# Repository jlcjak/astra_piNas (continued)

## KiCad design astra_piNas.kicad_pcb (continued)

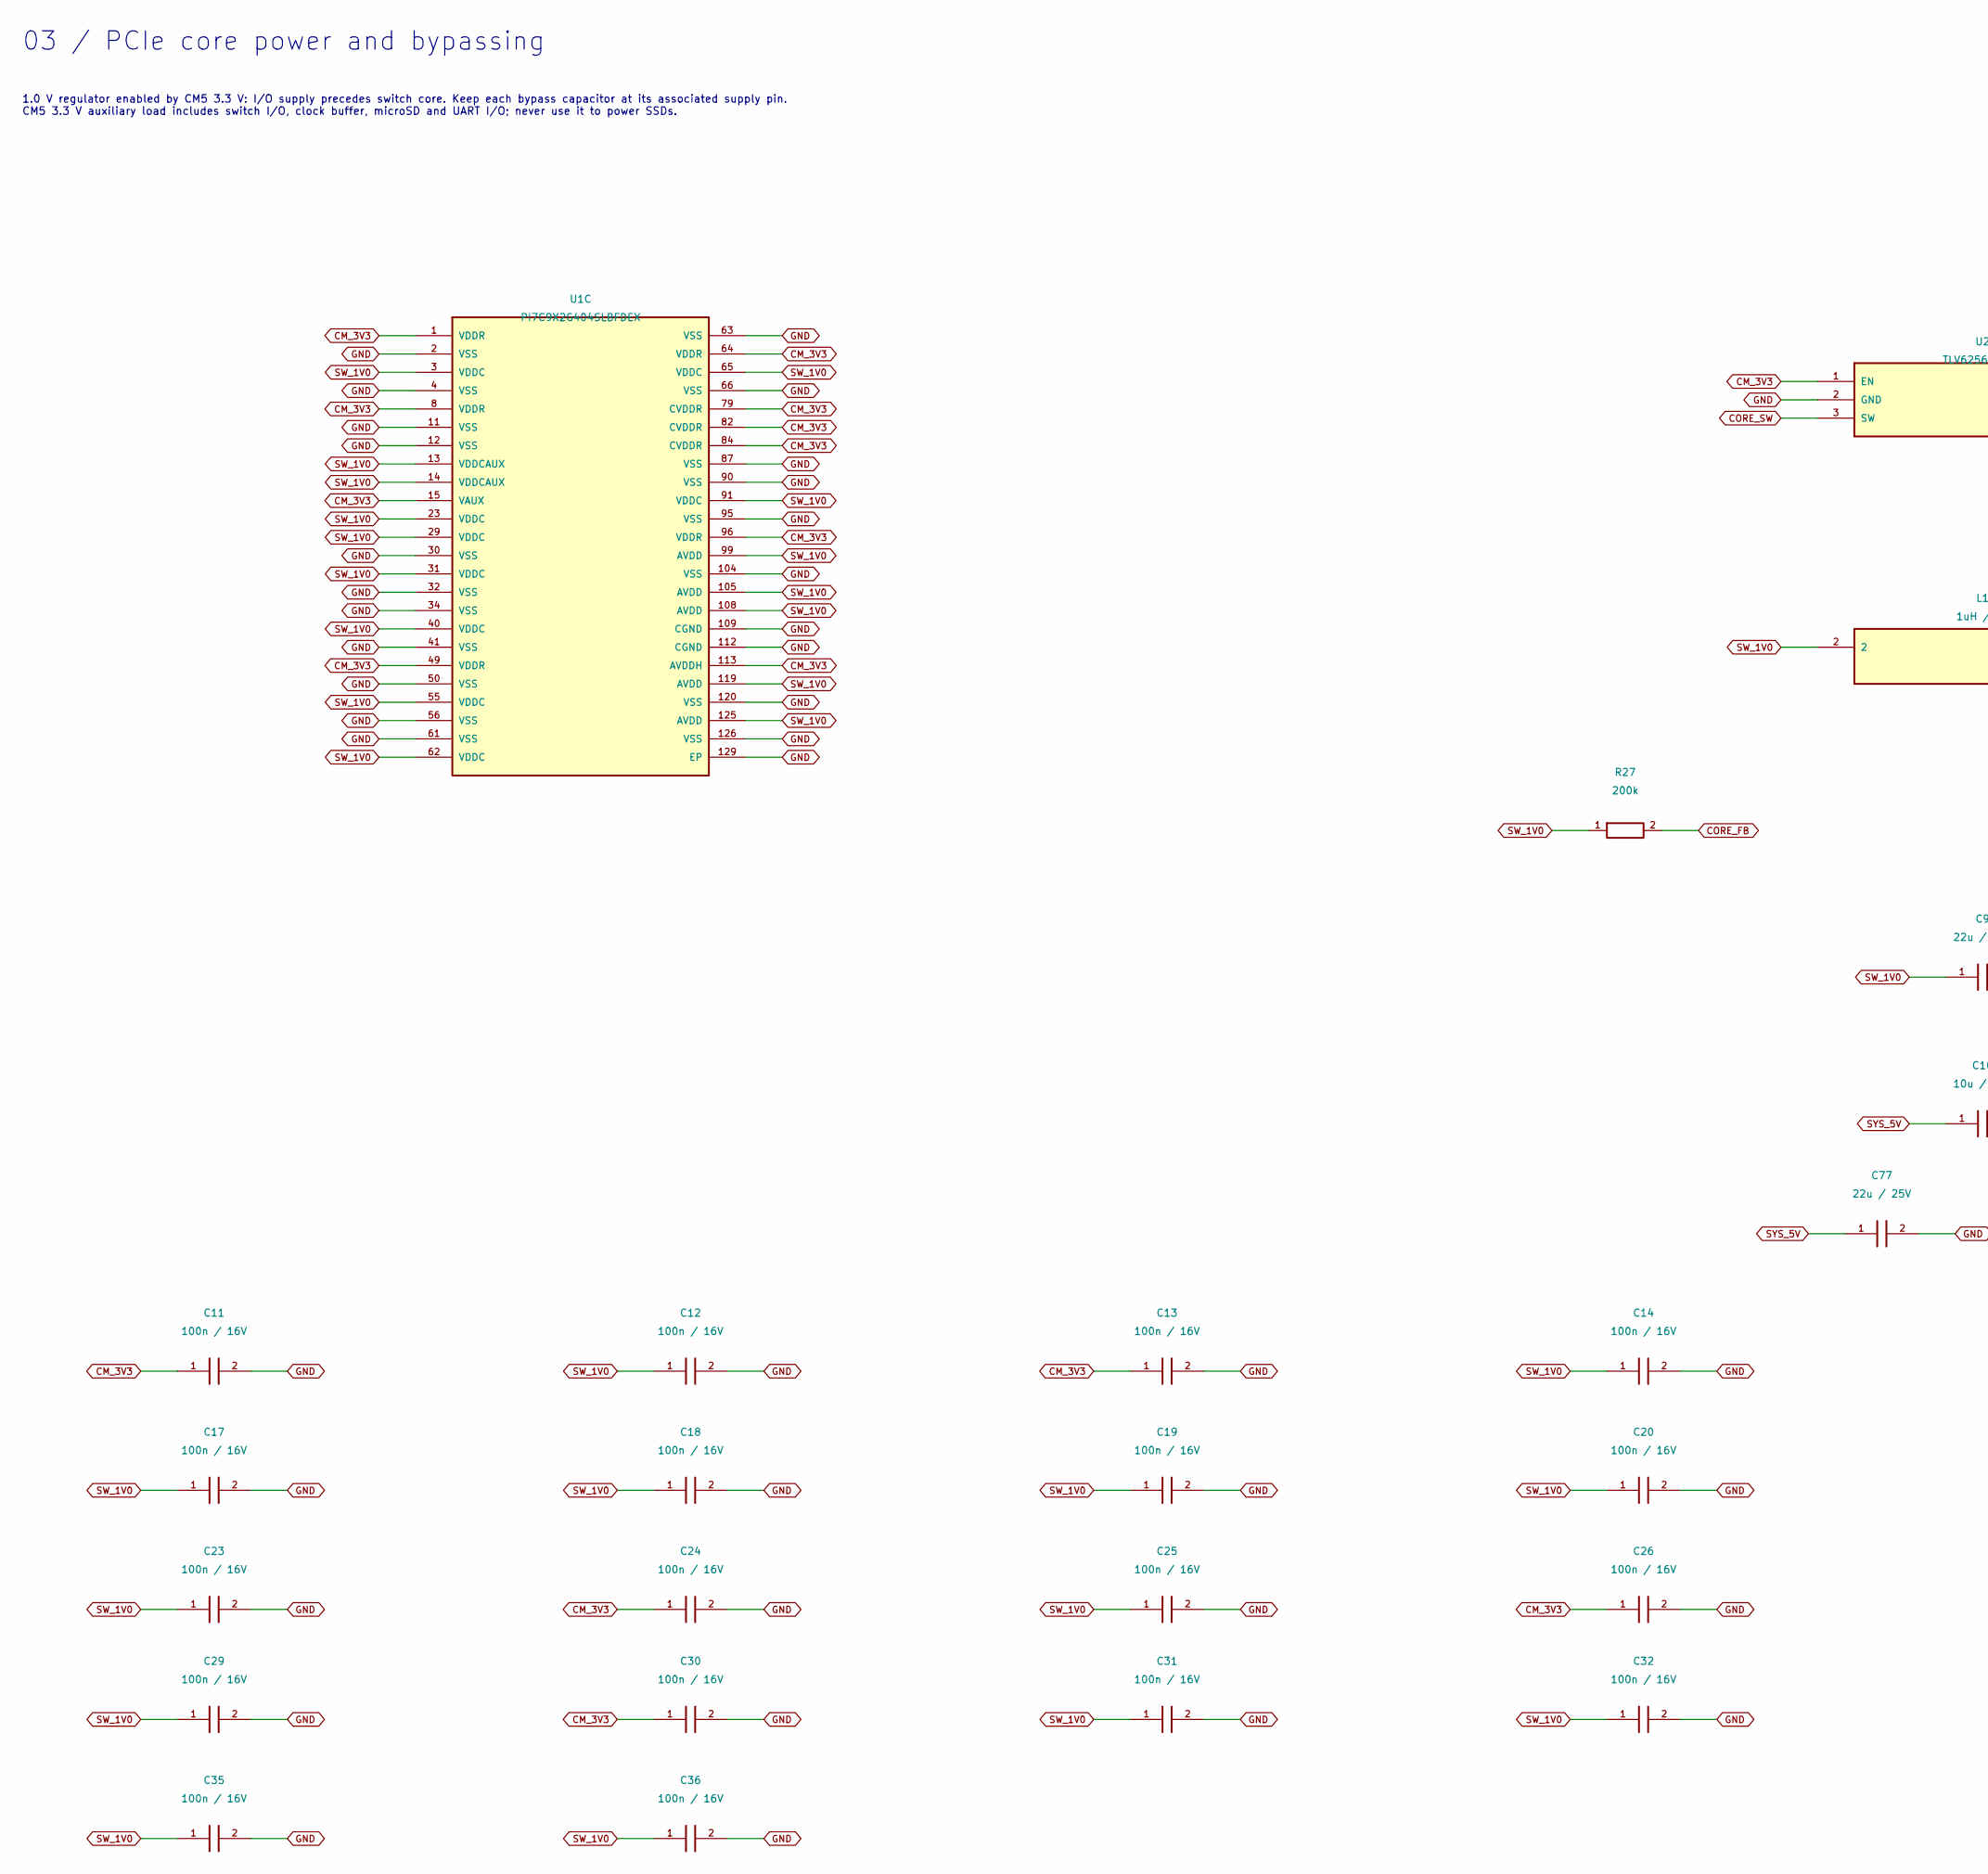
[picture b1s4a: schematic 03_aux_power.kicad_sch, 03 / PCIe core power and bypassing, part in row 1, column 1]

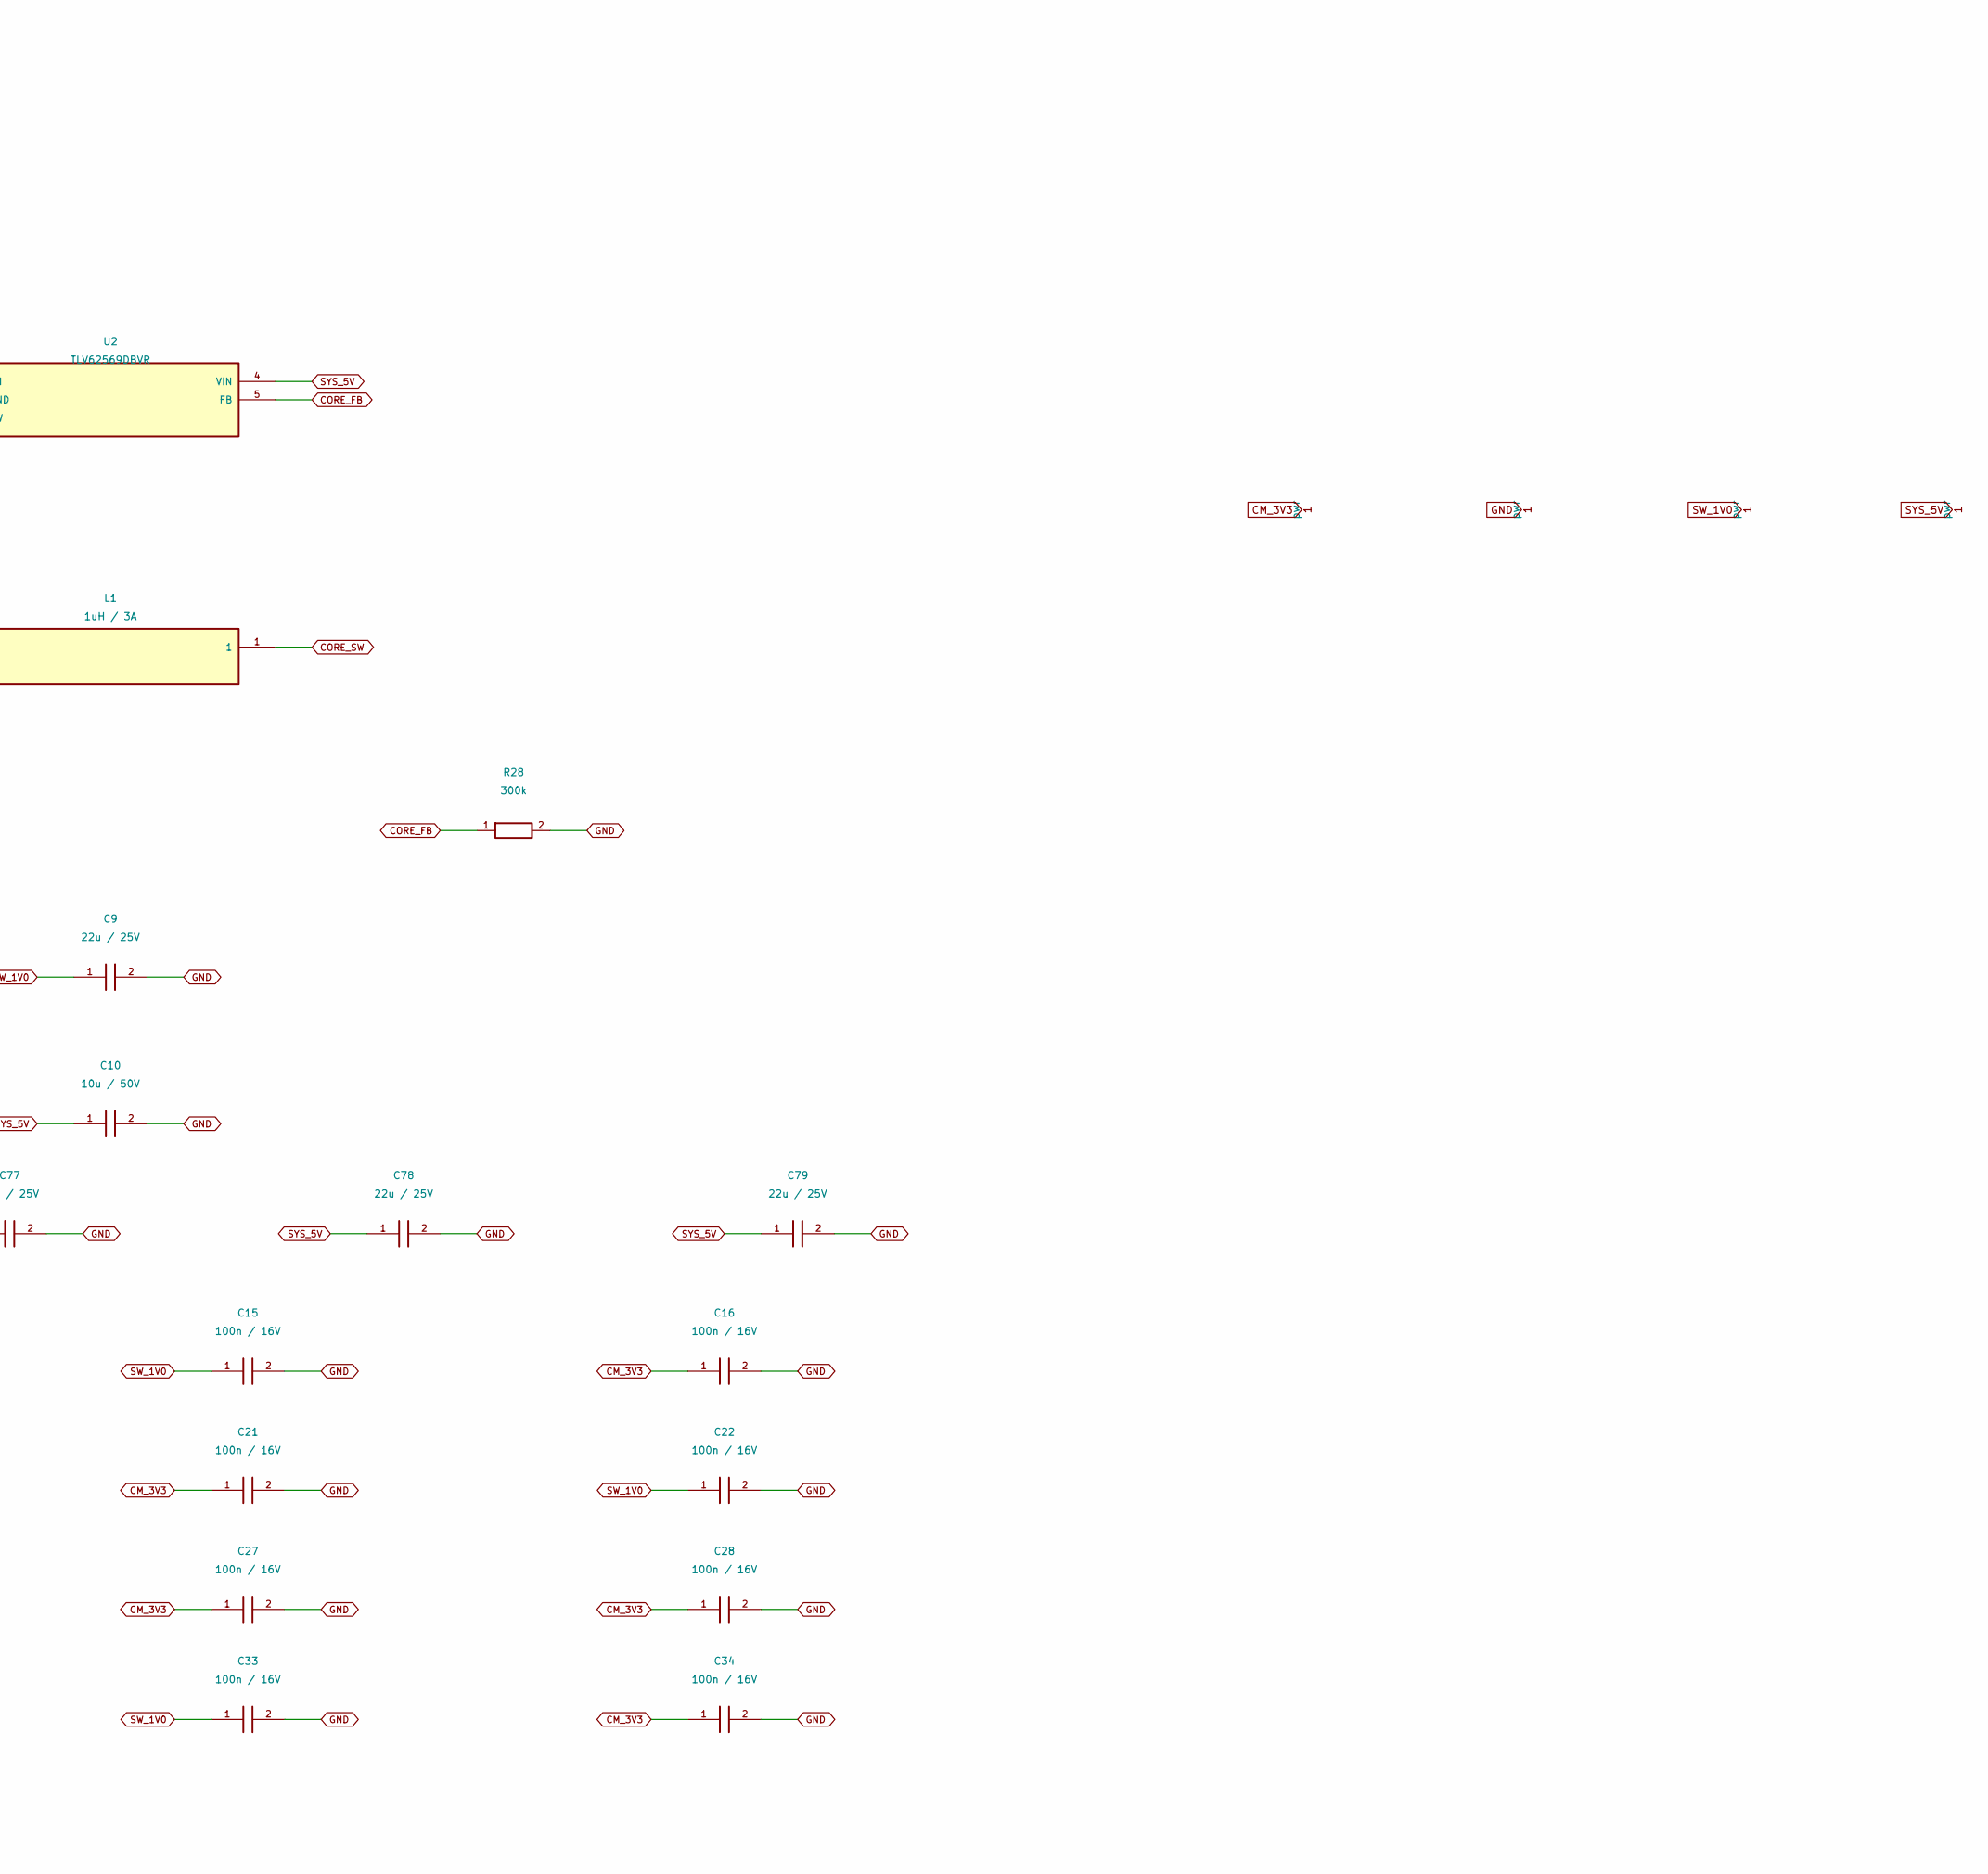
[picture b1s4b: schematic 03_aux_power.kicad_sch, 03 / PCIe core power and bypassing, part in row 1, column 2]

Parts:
C9, C77, C78, C79: 22u / 25V; C_0805_2012Metric; MANUFACTURER PART NUMBER CL21A226MAQNNNE; LCSC Part Number C45783
C10: 10u / 50V; C_1206_3216Metric; MANUFACTURER PART NUMBER CL31B106KAHNNNE; LCSC Part Number C14860
C11, C12, C13, C14, C15, C16, C17, C18, C19, C20, C21, C22, C23, C24, C25, C26, C27, C28, C29, C30, C31, C32, C33, C34, C35, C36: 100n / 16V; C_0402_1005Metric; MANUFACTURER PART NUMBER CL05B104KO5NNNC; LCSC Part Number C1525
L1: 1uH / 3A; IND-SMD_L2.5-W2.0-1; MANUFACTURER PART NUMBER VLS252010HBX-1R0M-1; LCSC Part Number C88211
R27: 200k; R_0603_1608Metric; MANUFACTURER PART NUMBER 0603WAF2003T5E; LCSC Part Number C25811
R28: 300k; R_0603_1608Metric; MANUFACTURER PART NUMBER 0603WAF3003T5E; LCSC Part Number C23024
U1: PI7C9X2G404SLBFDEX; LQFP-128_L14.0-W14.0-P0.40-LS16.0-BL-EP5.8; MANUFACTURER PART NUMBER PI7C9X2G404SLBFDEX; LCSC Part Number C500767
U2: TLV62569DBVR; SOT-23-5_L3.0-W1.7-P0.95-LS2.8-BR; MANUFACTURER PART NUMBER TLV62569DBVR; LCSC Part Number C141836

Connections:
CM_3V3: C11.1, C13.1, C16.1, C21.1, C24.1, C26.1, C27.1, C28.1, C30.1, C34.1, U1.1 (VDDR), U1.8 (VDDR), U1.15 (VAUX), U1.49 (VDDR), U1.64 (VDDR), U1.79 (CVDDR), U1.82 (CVDDR), U1.84 (CVDDR), U1.96 (VDDR), U1.113 (AVDDH), U2.1 (EN); also elsewhere on the board
CORE_FB: R27.2, R28.1, U2.5 (FB)
CORE_SW: L1.1, U2.3 (SW)
GND: C9.2, C10.2, C11.2, C12.2, C13.2, C14.2, C15.2, C16.2, C17.2, C18.2, C19.2, C20.2, C21.2, C22.2, C23.2, C24.2, C25.2, C26.2, C27.2, C28.2, C29.2, C30.2, C31.2, C32.2, C33.2, C34.2, C35.2, C36.2, C77.2, C78.2, C79.2, R28.2, U1.2 (VSS), U1.4 (VSS), U1.11 (VSS), U1.12 (VSS), U1.30 (VSS), U1.32 (VSS), U1.34 (VSS), U1.41 (VSS), U1.50 (VSS), U1.56 (VSS), U1.61 (VSS), U1.63 (VSS), U1.66 (VSS), U1.87 (VSS), U1.90 (VSS), U1.95 (VSS), U1.104 (VSS), U1.109 (CGND), U1.112 (CGND), U1.120 (VSS), U1.126 (VSS), U1.129 (EP), U2.2 (GND); also elsewhere on the board
SW_1V0: C9.1, C12.1, C14.1, C15.1, C17.1, C18.1, C19.1, C20.1, C22.1, C23.1, C25.1, C29.1, C31.1, C32.1, C33.1, C35.1, C36.1, L1.2, R27.1, U1.3 (VDDC), U1.13 (VDDCAUX), U1.14 (VDDCAUX), U1.23 (VDDC), U1.29 (VDDC), U1.31 (VDDC), U1.40 (VDDC), U1.55 (VDDC), U1.62 (VDDC), U1.65 (VDDC), U1.91 (VDDC), U1.99 (AVDD), U1.105 (AVDD), U1.108 (AVDD), U1.119 (AVDD), U1.125 (AVDD)
SYS_5V: C10.1, C77.1, C78.1, C79.1, U2.4 (VIN); also elsewhere on the board

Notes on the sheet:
03 / PCIe core power and bypassing
1.0 V regulator enabled by CM5 3.3 V: I/O supply precedes switch core. Keep each bypass capacitor at its associated supply pin. CM5 3.3 V auxiliary load includes switch I/O, clock buffer, microSD and UART I/O; never use it to power SSDs.

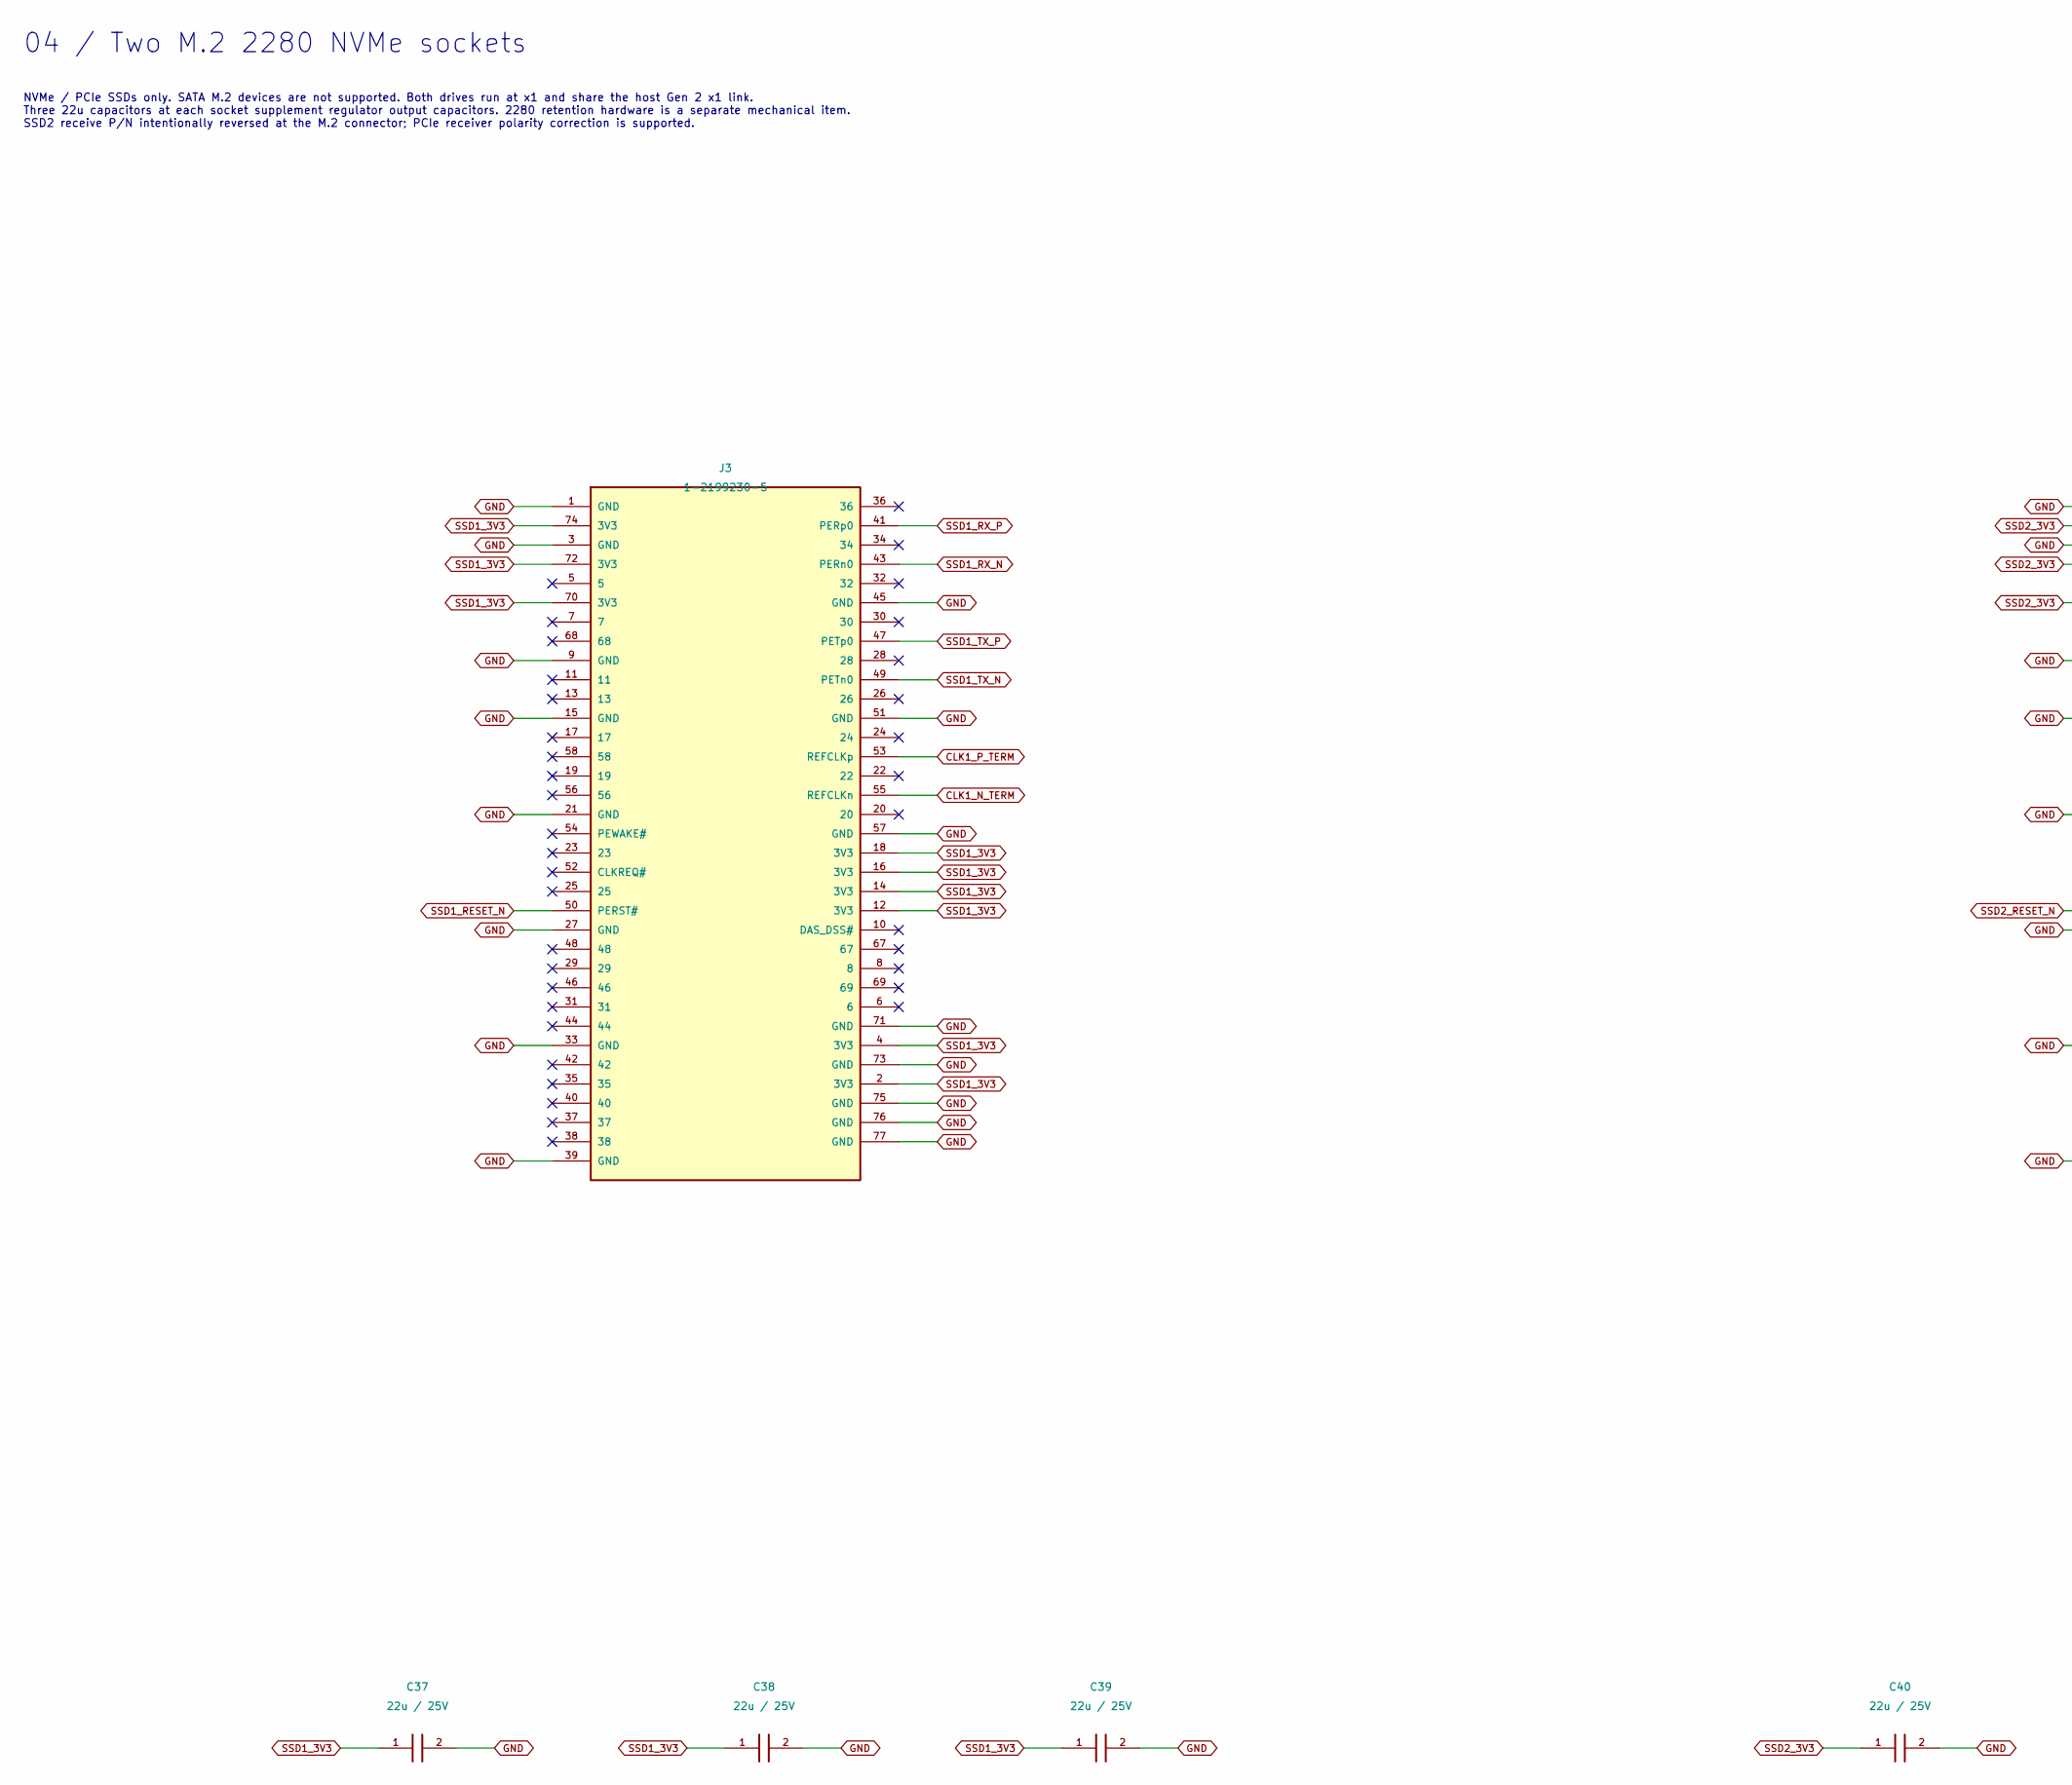
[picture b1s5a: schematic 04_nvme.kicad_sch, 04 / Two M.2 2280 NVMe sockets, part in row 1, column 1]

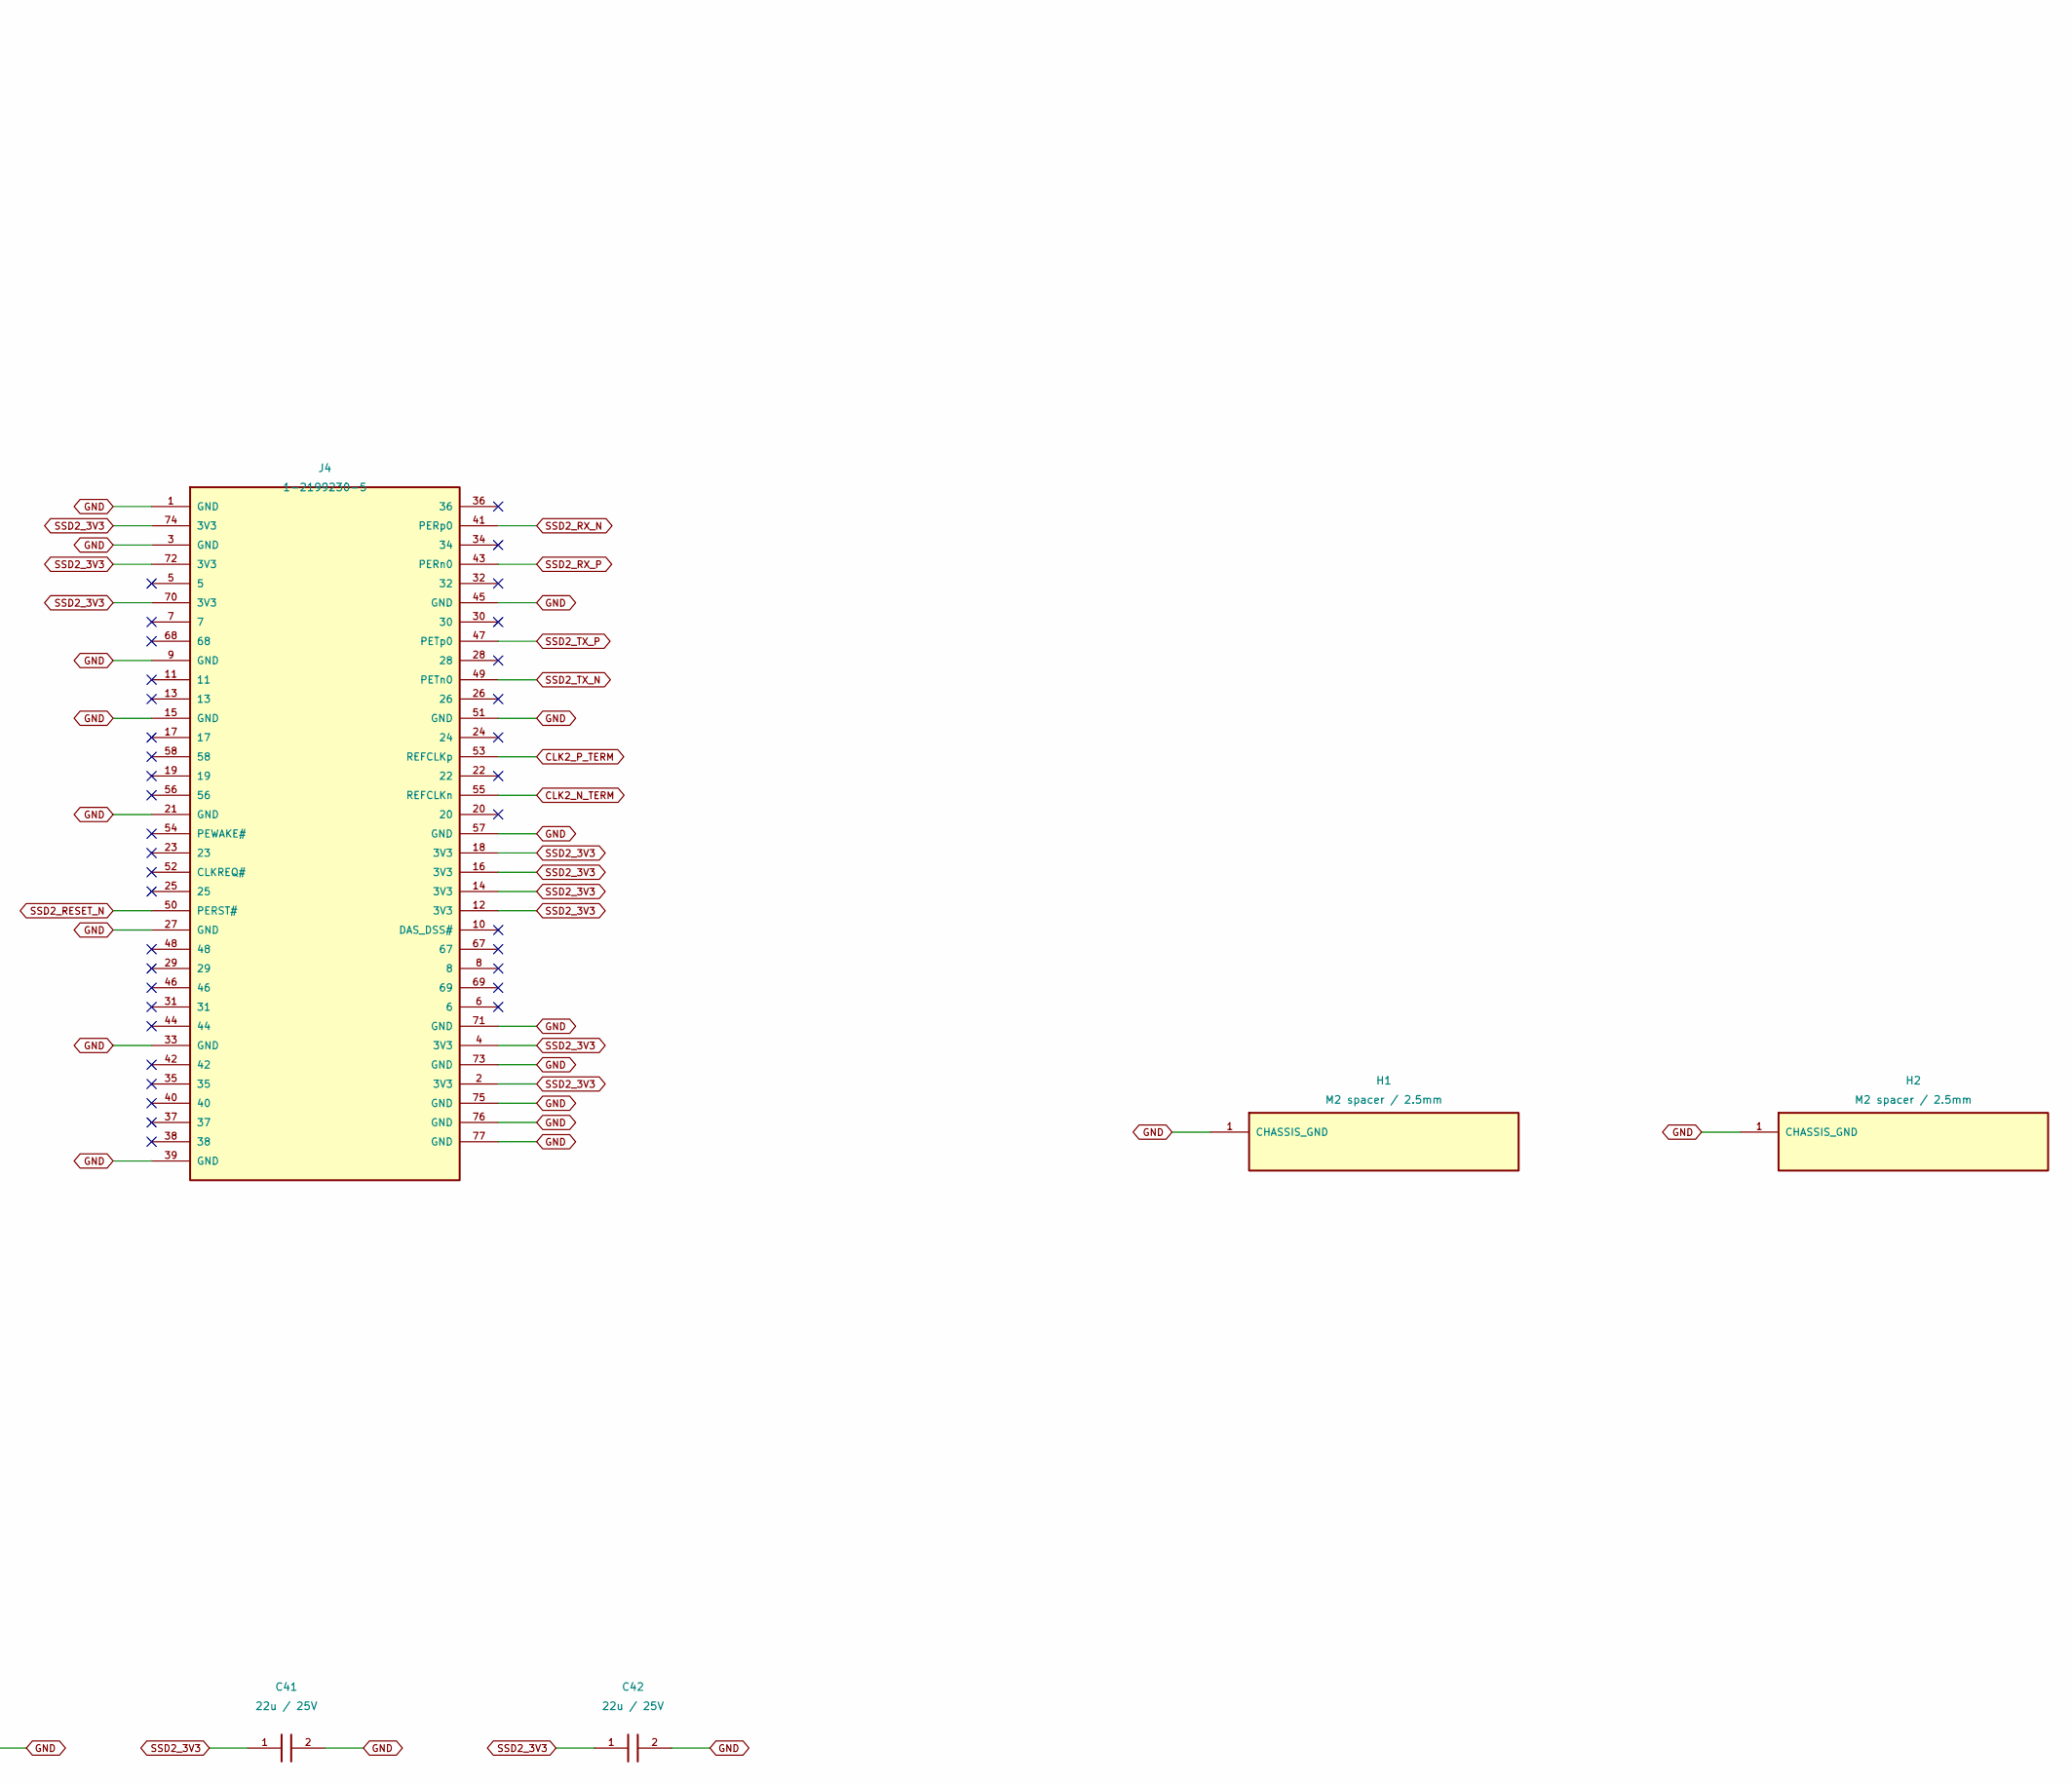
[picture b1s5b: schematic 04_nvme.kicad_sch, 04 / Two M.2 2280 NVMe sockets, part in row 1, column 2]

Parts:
C37, C38, C39, C40, C41, C42: 22u / 25V; C_0805_2012Metric; MANUFACTURER PART NUMBER CL21A226MAQNNNE; LCSC Part Number C45783
H1, H2: M2 spacer / 2.5mm; YIYUAN_SMTSOM225BTR; MANUFACTURER PART NUMBER SMTSOM225BTR; LCSC Part Number C5301773
J3, J4: 1-2199230-5; PCIE-SMD_75P-P0.50_1-2199230-5; MANUFACTURER PART NUMBER 1-2199230-5; LCSC Part Number C590854

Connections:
CLK1_N_TERM: J3.55 (REFCLKn); also elsewhere on the board
CLK1_P_TERM: J3.53 (REFCLKp); also elsewhere on the board
CLK2_N_TERM: J4.55 (REFCLKn); also elsewhere on the board
CLK2_P_TERM: J4.53 (REFCLKp); also elsewhere on the board
GND: C37.2, C38.2, C39.2, C40.2, C41.2, C42.2, H1.1, H2.1, J3.1 (GND), J3.3 (GND), J3.9 (GND), J3.15 (GND), J3.21 (GND), J3.27 (GND), J3.33 (GND), J3.39 (GND), J3.45 (GND), J3.51 (GND), J3.57 (GND), J3.71 (GND), J3.73 (GND), J3.75 (GND), J3.76 (GND), J3.77 (GND), J4.1 (GND), J4.3 (GND), J4.9 (GND), J4.15 (GND), J4.21 (GND), J4.27 (GND), J4.33 (GND), J4.39 (GND), J4.45 (GND), J4.51 (GND), J4.57 (GND), J4.71 (GND), J4.73 (GND), J4.75 (GND), J4.76 (GND), J4.77 (GND); also elsewhere on the board
SSD1_3V3: C37.1, C38.1, C39.1, J3.2 (3V3), J3.4 (3V3), J3.12 (3V3), J3.14 (3V3), J3.16 (3V3), J3.18 (3V3), J3.70 (3V3), J3.72 (3V3), J3.74 (3V3); also elsewhere on the board
SSD1_RESET_N: J3.50 (PERST#); also elsewhere on the board
SSD1_RX_N: J3.43 (PERn0); also elsewhere on the board
SSD1_RX_P: J3.41 (PERp0); also elsewhere on the board
SSD1_TX_N: J3.49 (PETn0); also elsewhere on the board
SSD1_TX_P: J3.47 (PETp0); also elsewhere on the board
SSD2_3V3: C40.1, C41.1, C42.1, J4.2 (3V3), J4.4 (3V3), J4.12 (3V3), J4.14 (3V3), J4.16 (3V3), J4.18 (3V3), J4.70 (3V3), J4.72 (3V3), J4.74 (3V3); also elsewhere on the board
SSD2_RESET_N: J4.50 (PERST#); also elsewhere on the board
SSD2_RX_N: J4.41 (PERp0); also elsewhere on the board
SSD2_RX_P: J4.43 (PERn0); also elsewhere on the board
SSD2_TX_N: J4.49 (PETn0); also elsewhere on the board
SSD2_TX_P: J4.47 (PETp0); also elsewhere on the board

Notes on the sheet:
04 / Two M.2 2280 NVMe sockets
NVMe / PCIe SSDs only. SATA M.2 devices are not supported. Both drives run at x1 and share the host Gen 2 x1 link. Three 22u capacitors at each socket supplement regulator output capacitors. 2280 retention hardware is a separate mechanical item. SSD2 receive P/N intentionally reversed at the M.2 co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
